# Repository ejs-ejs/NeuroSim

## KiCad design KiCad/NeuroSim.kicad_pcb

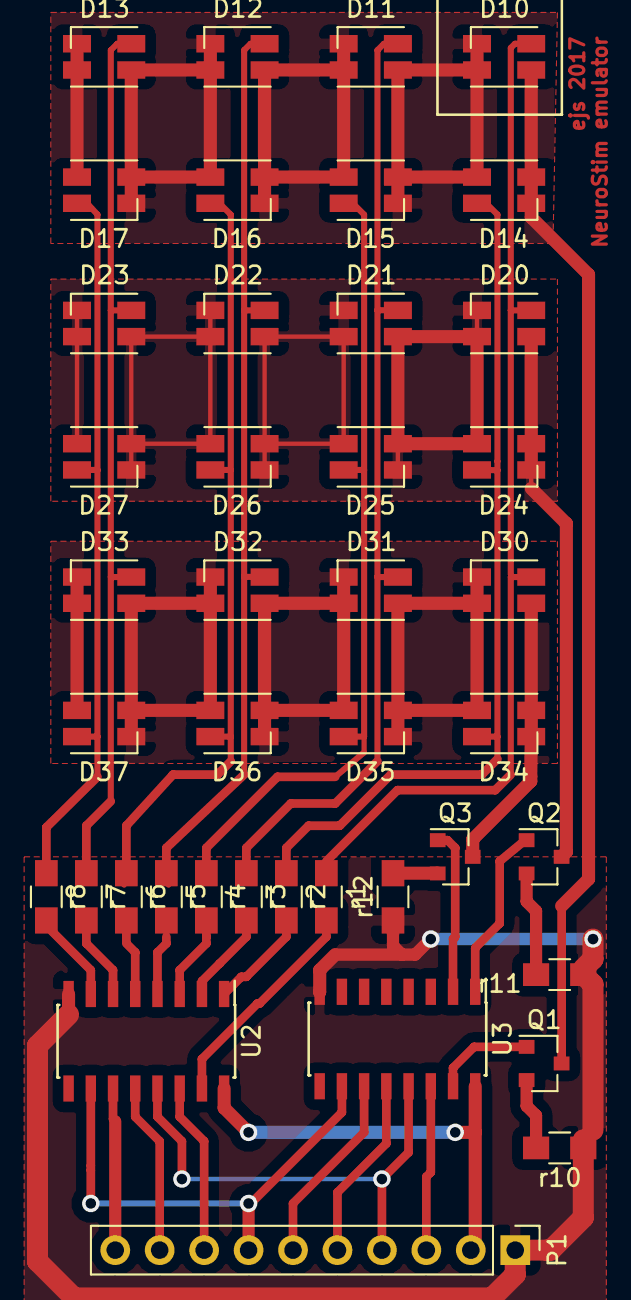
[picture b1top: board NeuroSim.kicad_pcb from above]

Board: 2 copper layers, 41 parts (0 on the bottom side), 35 nets.

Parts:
D10, D11, D12, D13, D14, D15, D16, D17, D20, D21, D22, D23, D24, D25, D26, D27, D30, D31, D32, D33, D34, D35, D36, D37: LED; LED_Osram-PLCC4-maxspace
P1: CONN_01X10; Pin_Header_Straight_1x10_Pitch2.54mm
Q1, Q2, Q3: BC817-40; SOT-23
U2, U3: 74LS595; SOIC-16_3.9x9.9mm_Pitch1.27mm
r1, r2, r3, r4, r5, r6, r7, r8: 150; R_0805_HandSoldering
r10, r11, r12: 4k7; R_0805_HandSoldering

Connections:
/a: D10.2, D20.2, D30.2, r1.1
/b: D11.2, D21.2, D31.2, r3.1
/c: D12.2, D22.2, D32.2, r5.1
/d: D13.2, D23.2, D33.2, r7.1
/e: D14.2, D24.2, D34.2, r2.1
/f: D15.2, D25.2, D35.2, r4.1
/g: D16.2, D26.2, D36.2, r6.1
/h: D17.2, D27.2, D37.2, r8.1
/r1: D10.1, D11.1, D12.1, D13.1, D14.1, D15.1, D16.1, D17.1, Q1.3
/r2: D20.1, D21.1, D22.1, D23.1, D24.1, D25.1, D26.1, D27.1, Q2.3
/r3: D30.1, D31.1, D32.1, D33.1, D34.1, D35.1, D36.1, D37.1, Q3.3
GND: P1.1, U2.8, U3.8, r10.1, r11.1, r12.1
unnamed: P1.3, U3.14
unnamed: P1.4, U2.13, U3.13
unnamed: P1.5, U3.12
unnamed: P1.6, U3.11
unnamed: P1.7, U2.10, U3.10
unnamed: P1.8, U2.14
unnamed: P1.9, U2.12
unnamed: P1.10, U2.11
unnamed: Q1.1, U3.15
unnamed: Q1.2, r10.2
unnamed: Q2.1, U3.1
unnamed: Q2.2, r11.2
unnamed: Q3.1, U3.2
unnamed: Q3.2, r12.2
unnamed: U2.1, r2.2
unnamed: U2.2, r3.2
unnamed: U2.3, r4.2
unnamed: U2.4, r5.2
unnamed: U2.5, r6.2
unnamed: U2.6, r7.2
unnamed: U2.7, r8.2
unnamed: U2.15, r1.2
VCC: P1.2, U2.16, U3.16

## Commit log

2017-02-28 :octocat: Added .gitattributes & .gitignore files
2017-02-28 1st commit
    Initial commit
